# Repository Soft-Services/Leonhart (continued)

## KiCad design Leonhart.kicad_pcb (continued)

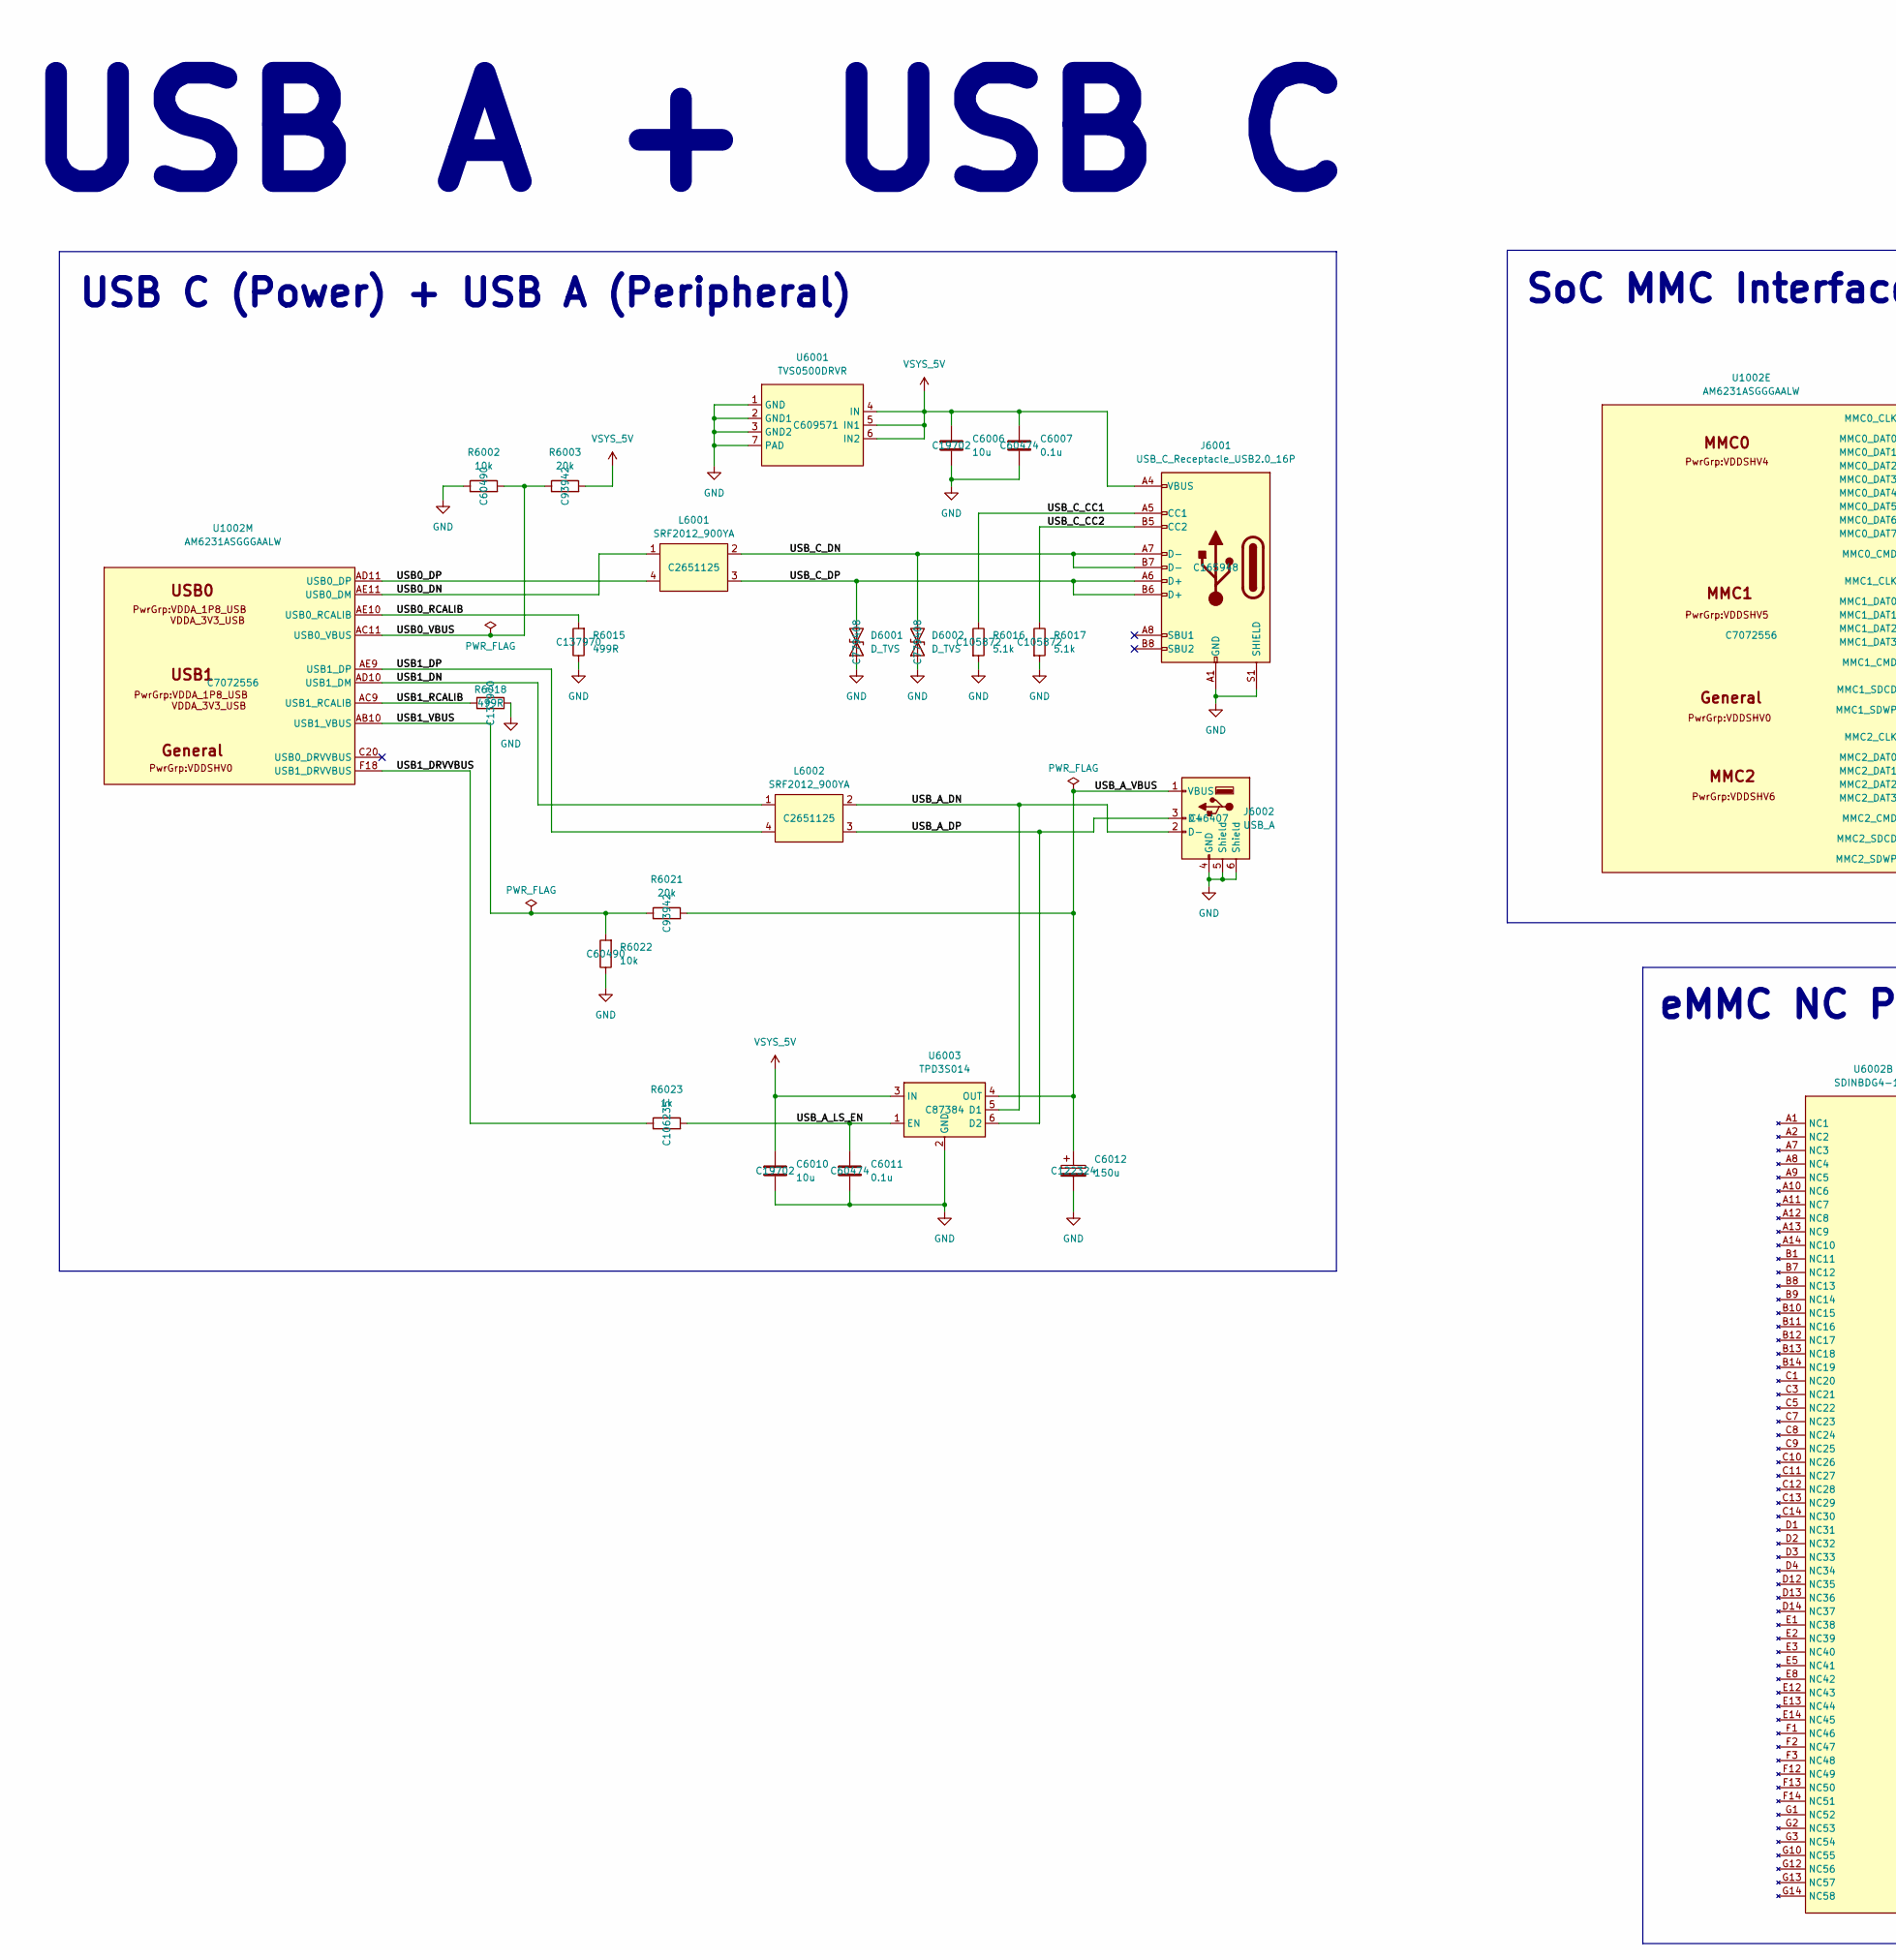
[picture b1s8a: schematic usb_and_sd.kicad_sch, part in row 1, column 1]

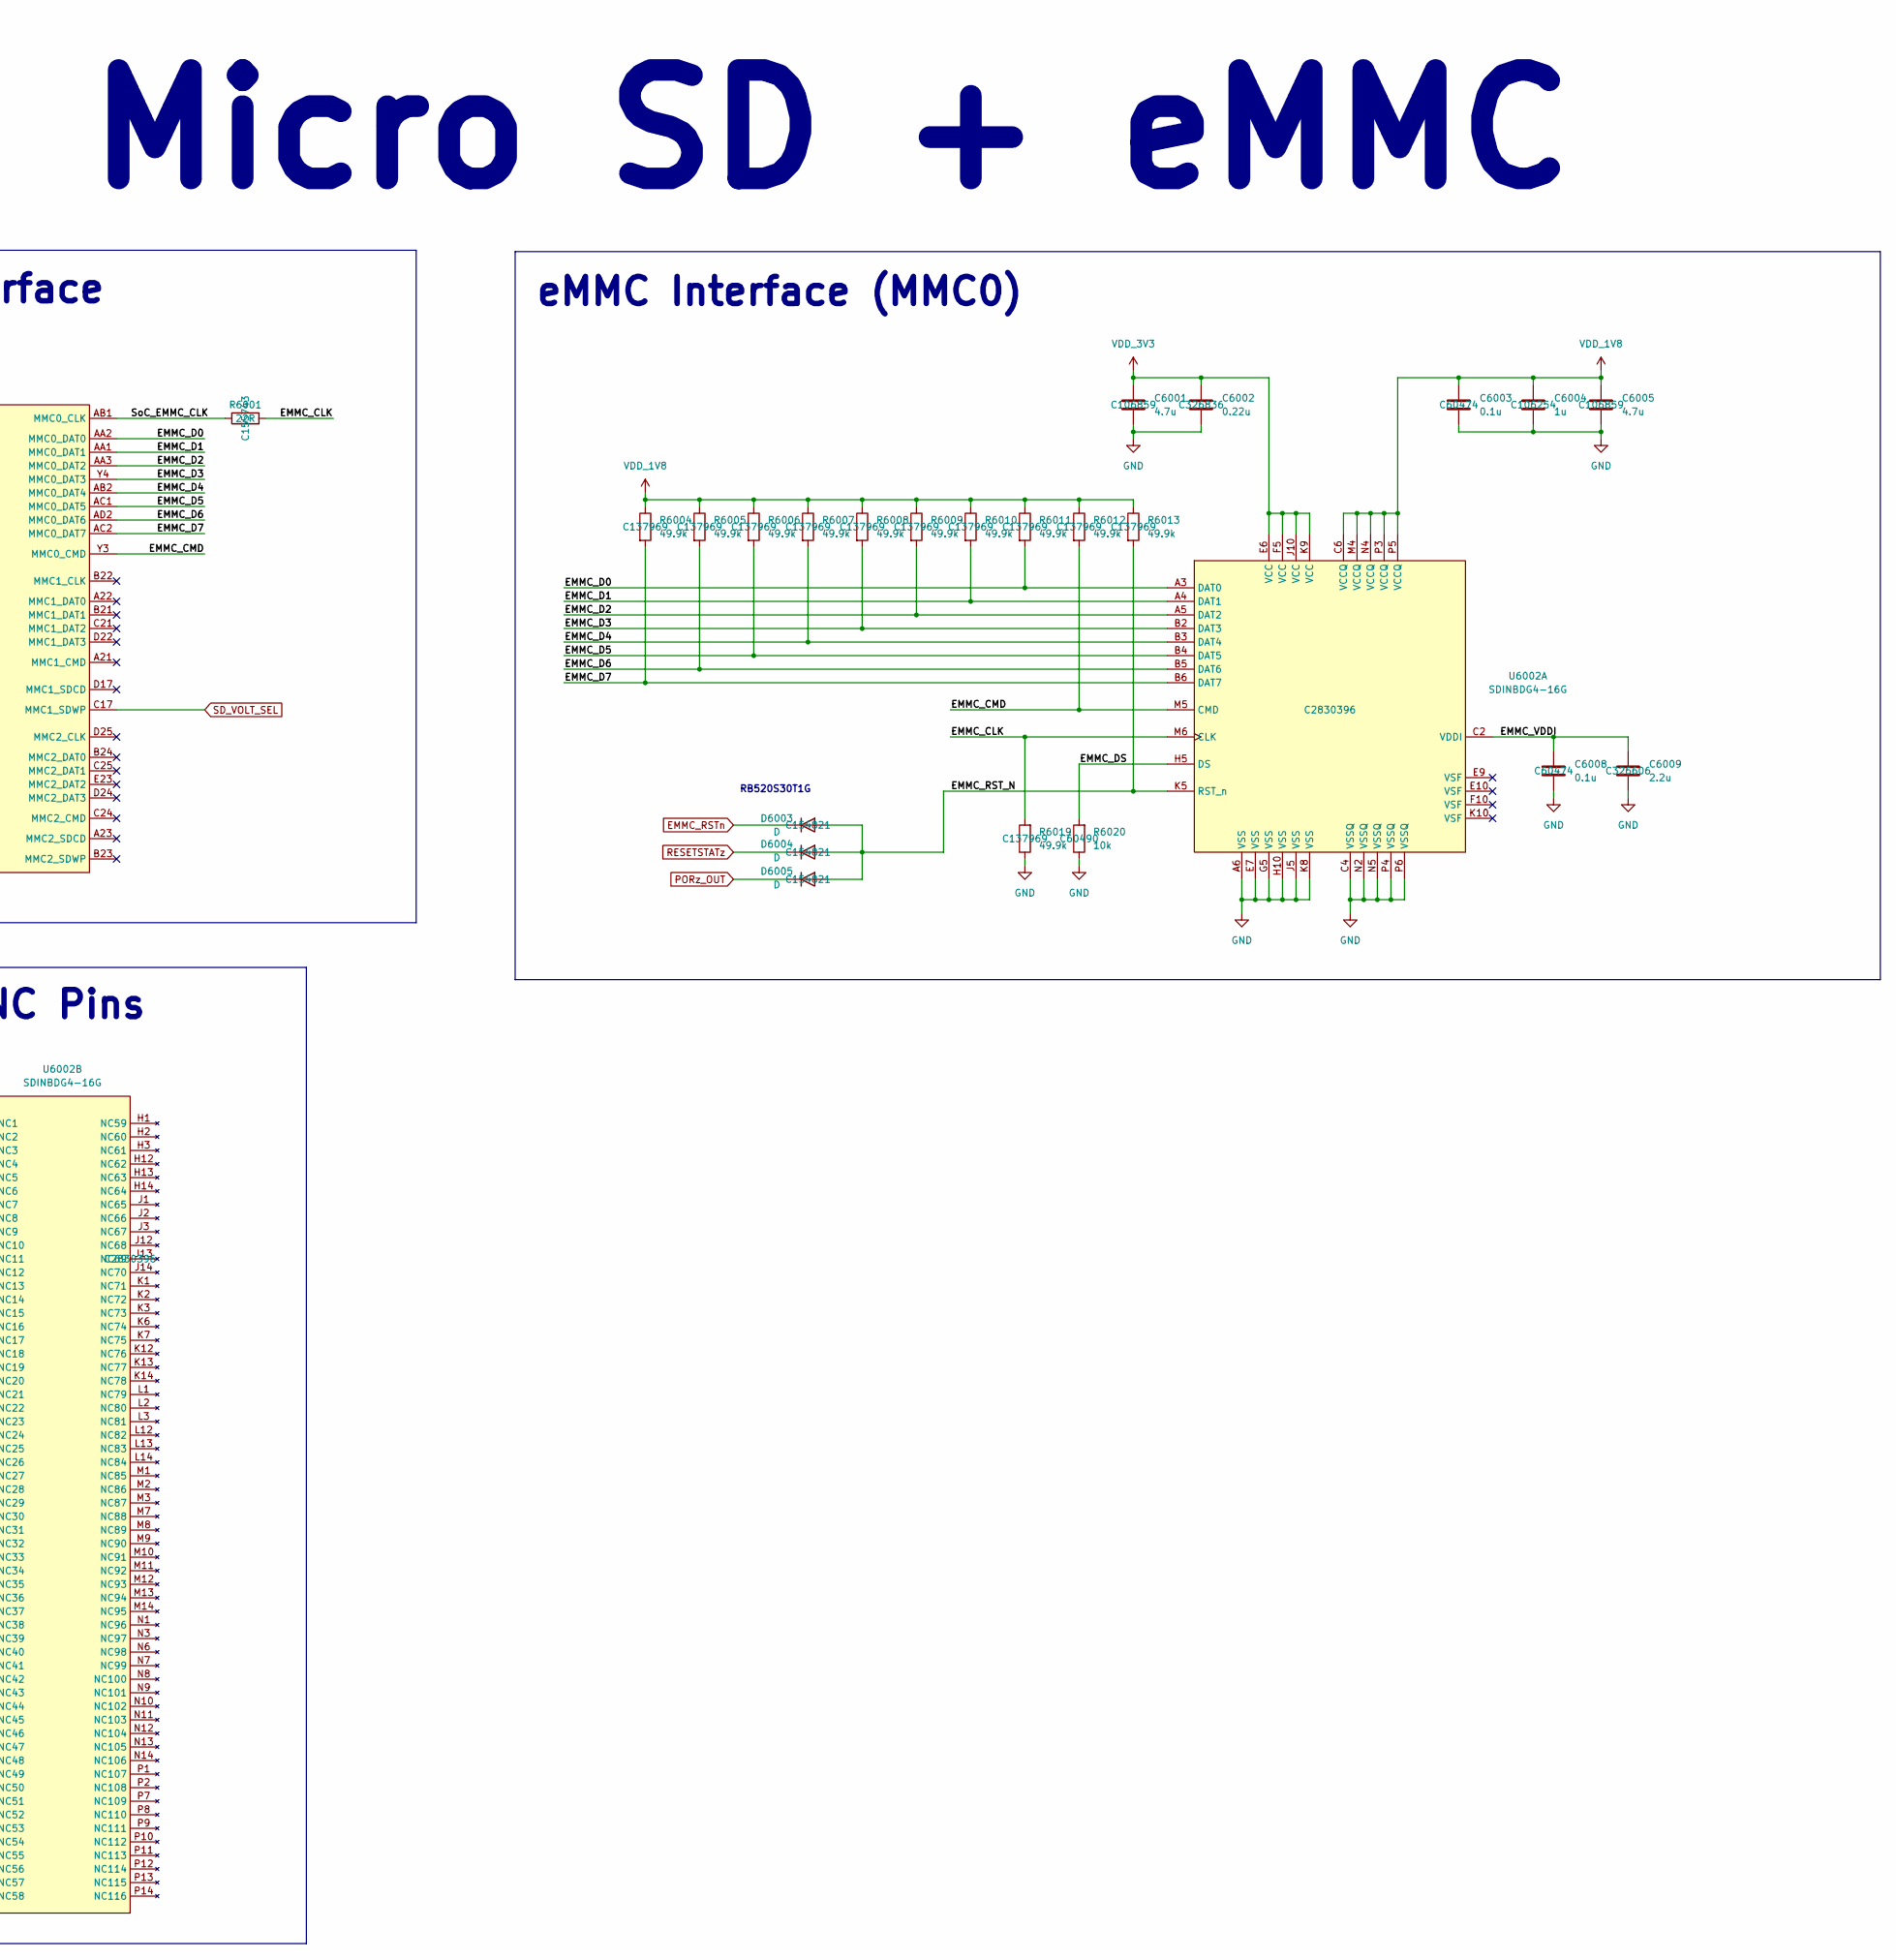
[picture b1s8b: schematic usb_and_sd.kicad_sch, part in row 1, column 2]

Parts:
C6001, C6005: 4.7u; C_0402_1005Metric; JLCPCB Part# C106859
C6002: 0.22u; C_0402_1005Metric; JLCPCB Part# C326836
C6003, C6007, C6008, C6011: 0.1u; C_0402_1005Metric; JLCPCB Part# C60474
C6004: 1u; C_0402_1005Metric; JLCPCB Part# C106254
C6006, C6010: 10u; C_0603_1608Metric; JLCPCB Part# C19702
C6009: 2.2u; C_0402_1005Metric; JLCPCB Part# C326606
C6012: 150u; CP_EIA-7343-31_Kemet-D; JLCPCB Part# C122324
D6001, D6002: D_TVS; TPD1E1B04DPYR; JLCPCB Part# C779408
D6003, D6004, D6005: D; D_SOD-523; JLCPCB Part# C154821
J6001: USB_C_Receptacle_USB2.0_16P; USB_C_Receptacle_HRO_TYPE-C-31-M-12; JLCPCB Part# C165948
J6002: USB_A; 902131A1011D10100; JLCPCB Part# C46407
L6001, L6002: SRF2012_900YA; SRF2012-900YA; JLCPCB Part# C2651125
R6001: 22R; R_0201_0603Metric; JLCPCB Part# C155743
R6002, R6020, R6022: 10k; R_0402_1005Metric; JLCPCB Part# C60490
R6003, R6021: 20k; R_0402_1005Metric; JLCPCB Part# C93942
R6004, R6005, R6006, R6007, R6008, R6009, R6010, R6011, R6012, R6013, R6019: 49.9k; R_0402_1005Metric; JLCPCB Part# C137969
R6015, R6018: 499R; R_0402_1005Metric; JLCPCB Part# C137970
R6016, R6017: 5.1k; R_0402_1005Metric; JLCPCB Part# C105872
R6023: 1k; R_0402_1005Metric; JLCPCB Part# C106235
U1002: AM6231ASGGGAALW; BGA425C50P25X25_1300X1300X89; JLCPCB Part# C7072556
U6001: TVS0500DRVR; WSON-6-1EP_2x2mm_P0.65mm_EP1x1.6mm; JLCPCB Part# C609571
U6002: SDINBDG4-16G; LFBGA-153_11.5x13mm_Layout14x14_P0.5mm; JLCPCB Part# C2830396
U6003: TPD3S014; SOT-23-6; JLCPCB Part# C87384

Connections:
/USB and MMC [6]/EMMC_CLK: R6001.2, R6019.2, U6002.M6 (CLK)
/USB and MMC [6]/EMMC_CMD: R6012.2, U1002.Y3 (MMC0_CMD), U6002.M5 (CMD)
/USB and MMC [6]/EMMC_D0: R6011.2, U1002.AA2 (MMC0_DAT0), U6002.A3 (DAT0)
/USB and MMC [6]/EMMC_D1: R6010.2, U1002.AA1 (MMC0_DAT1), U6002.A4 (DAT1)
/USB and MMC [6]/EMMC_D2: R6009.2, U1002.AA3 (MMC0_DAT2), U6002.A5 (DAT2)
/USB and MMC [6]/EMMC_D3: R6008.2, U1002.Y4 (MMC0_DAT3), U6002.B2 (DAT3)
/USB and MMC [6]/EMMC_D4: R6007.2, U1002.AB2 (MMC0_DAT4), U6002.B3 (DAT4)
/USB and MMC [6]/EMMC_D5: R6006.2, U1002.AC1 (MMC0_DAT5), U6002.B4 (DAT5)
/USB and MMC [6]/EMMC_D6: R6005.2, U1002.AD2 (MMC0_DAT6), U6002.B5 (DAT6)
/USB and MMC [6]/EMMC_D7: R6004.2, U1002.AC2 (MMC0_DAT7), U6002.B6 (DAT7)
/USB and MMC [6]/EMMC_DS: R6020.2, U6002.H5 (DS)
/USB and MMC [6]/EMMC_RST_N: D6003.2 (A), D6004.2 (A), D6005.2 (A), R6013.2, U6002.K5 (RST_n)
/USB and MMC [6]/EMMC_VDDI: C6008.1, C6009.1, U6002.C2 (VDDI)
/USB and MMC [6]/SoC_EMMC_CLK: R6001.1, U1002.AB1 (MMC0_CLK)
/USB and MMC [6]/USB0_DN: L6001.1, U1002.AE11 (USB0_DM)
/USB and MMC [6]/USB0_DP: L6001.4, U1002.AD11 (USB0_DP)
/USB and MMC [6]/USB0_RCALIB: R6015.2, U1002.AE10 (USB0_RCALIB)
/USB and MMC [6]/USB0_VBUS: R6002.2, R6003.1, U1002.AC11 (USB0_VBUS)
/USB and MMC [6]/USB1_DN: L6002.1, U1002.AD10 (USB1_DM)
/USB and MMC [6]/USB1_DP: L6002.4, U1002.AE9 (USB1_DP)
/USB and MMC [6]/USB1_DRVVBUS: R6023.1, U1002.F18 (USB1_DRVVBUS)
/USB and MMC [6]/USB1_RCALIB: R6018.2, U1002.AC9 (USB1_RCALIB)
/USB and MMC [6]/USB1_VBUS: R6021.1, R6022.2, U1002.AB10 (USB1_VBUS)
/USB and MMC [6]/USB_A_DN: J6002.2 (D-), L6002.2, U6003.5 (D1)
/USB and MMC [6]/USB_A_DP: J6002.3 (D+), L6002.3, U6003.6 (D2)
/USB and MMC [6]/USB_A_LS_EN: C6011.1, R6023.2, U6003.1 (EN)
/USB and MMC [6]/USB_A_VBUS: C6012.1, J6002.1 (VBUS), R6021.2, U6003.4 (OUT)
/USB and MMC [6]/USB_C_CC1: J6001.A5 (CC1), R6016.1
/USB and MMC [6]/USB_C_CC2: J6001.B5 (CC2), R6017.1
/USB and MMC [6]/USB_C_DN: D6002.2 (A2), J6001.A7 (D-), J6001.B7 (D-), L6001.2
/USB and MMC [6]/USB_C_DP: D6001.2 (A2), J6001.A6 (D+), J6001.B6 (D+), L6001.3
EMMC_RSTn: D6003.1 (K); also elsewhere on the board
GND: C6001.2, C6002.2, C6003.2, C6004.2, C6005.2, C6006.2, C6007.2, C6008.2, C6009.2, C6010.2, C6011.2, C6012.2, D6001.1 (A1), D6002.1 (A1), J6001.A1 (GND), J6001.A12 (GND), J6001.B1 (GND), J6001.B12 (GND), J6001.S1 (SHIELD), J6002.4 (GND), J6002.5 (Shield), J6002.6 (Shield), R6002.1, R6015.1, R6016.2, R6017.2, R6018.1, R6019.1, R6020.1, R6022.1, U6001.1 (GND), U6001.2 (GND1), U6001.3 (GND2), U6001.7 (PAD), U6002.A6 (VSS), U6002.C4 (VSSQ), U6002.E7 (VSS), U6002.G5 (VSS), U6002.H10 (VSS), U6002.J5 (VSS), U6002.K8 (VSS), U6002.N2 (VSSQ), U6002.N5 (VSSQ), U6002.P4 (VSSQ), U6002.P6 (VSSQ), U6003.2 (GND); also elsewhere on the board
PORz_OUT: D6005.1 (K); also elsewhere on the board
RESETSTATz: D6004.1 (K); also elsewhere on the board
SD_VOLT_SEL: U1002.C17 (MMC1_SDWP); also elsewhere on the board
VDD_1V8: C6003.1, C6004.1, C6005.1, R6004.1, R6005.1, R6006.1, R6007.1, R6008.1, R6009.1, R6010.1, R6011.1, R6012.1, R6013.1, U6002.C6 (VCCQ), U6002.M4 (VCCQ), U6002.N4 (VCCQ), U6002.P3 (VCCQ), U6002.P5 (VCCQ); also elsewhere on the board
VDD_3V3: C6001.1, C6002.1, U6002.E6 (VCC), U6002.F5 (VCC), U6002.J10 (VCC), U6002.K9 (VCC); also elsewhere on the board
VSYS_5V: C6006.1, C6007.1, C6010.1, J6001.A4 (VBUS), J6001.A9 (VBUS), J6001.B4 (VBUS), J6001.B9 (VBUS), R6003.2, U6001.4 (IN), U6001.5 (IN1), U6001.6 (IN2), U6003.3 (IN); also elsewhere on the board

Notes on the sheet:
USB C (Power) + USB A (Peripheral)
eMMC Interface (MMC0)
Micro SD + eMMC
RB520S30T1G
SoC MMC Interface
eMMC NC Pins
USB A + USB C

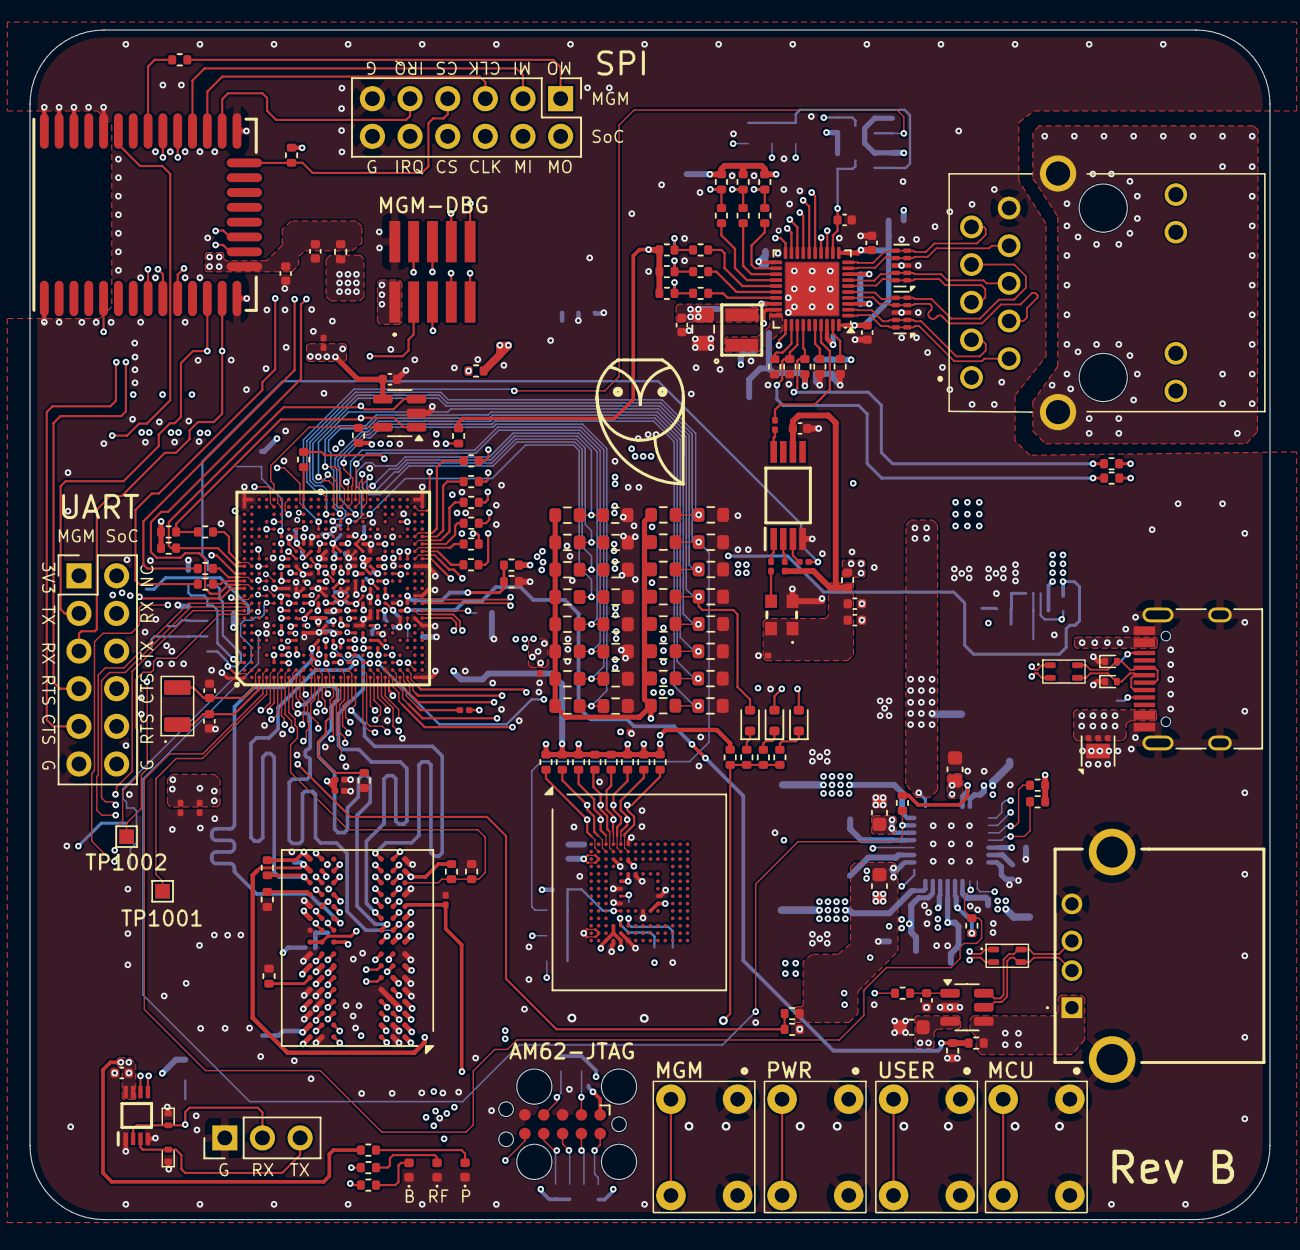
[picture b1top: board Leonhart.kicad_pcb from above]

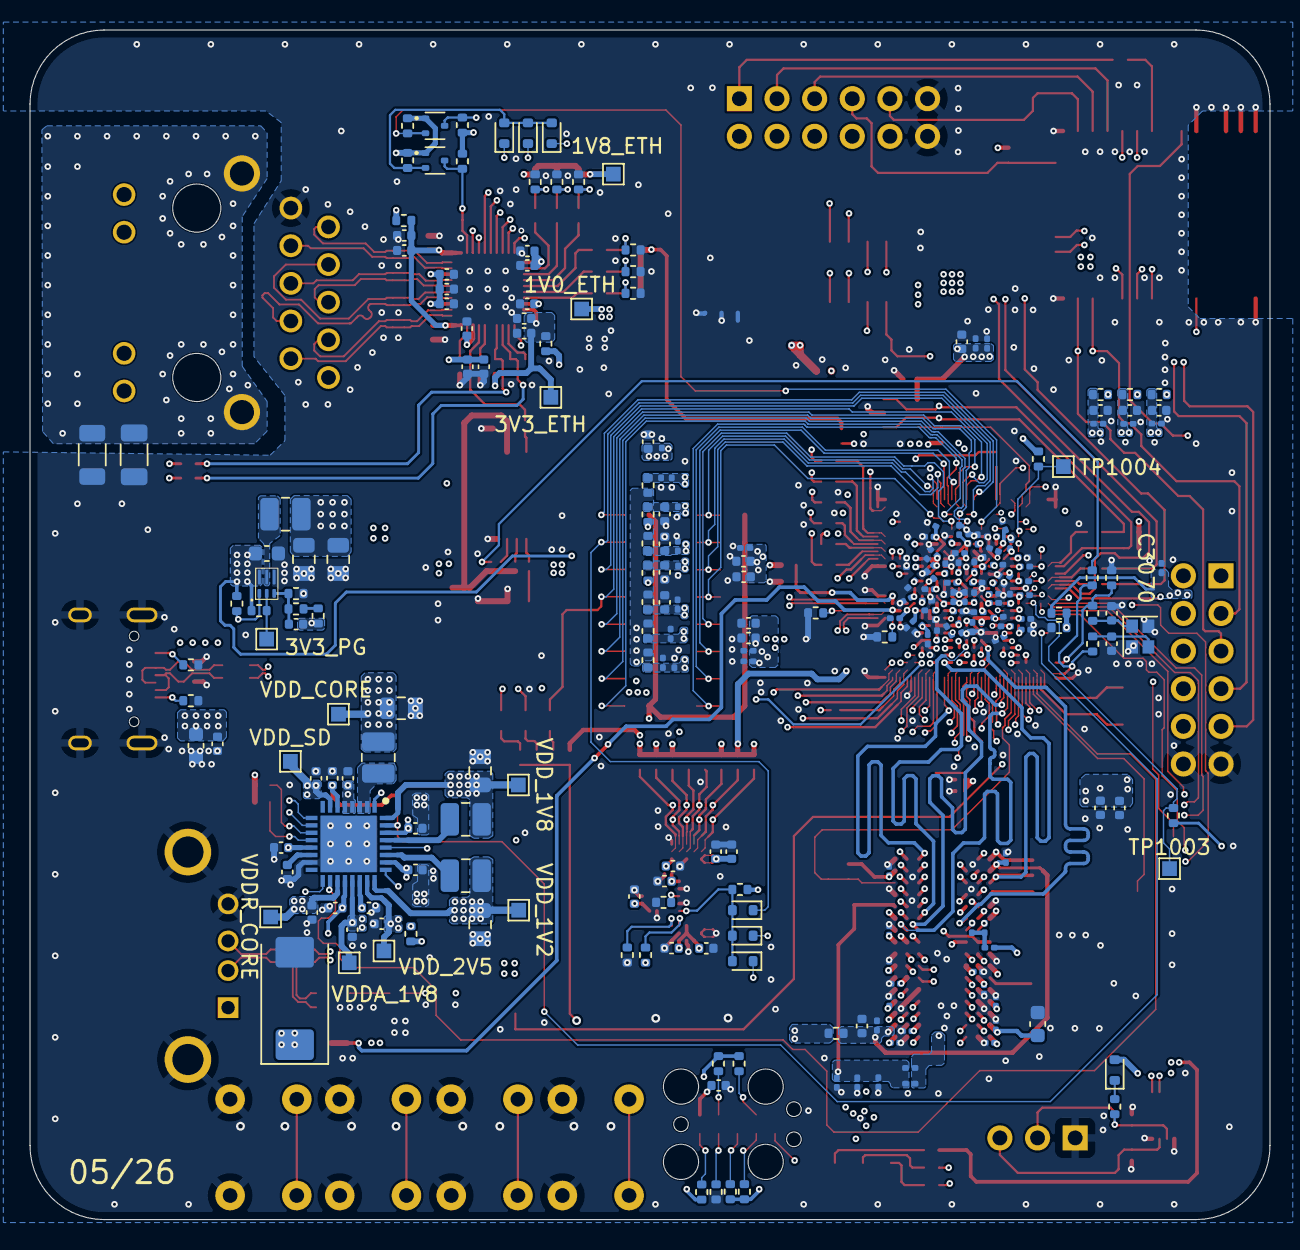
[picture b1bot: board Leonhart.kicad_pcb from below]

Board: 8 copper layers, 83.7 x 80.3 mm, 422 parts (245 on the bottom side), 275 nets.

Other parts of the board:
1V0_ETH, 1V8_ETH, 3V3_ETH, 3V3_PG: TestPoint; TestPoint_Pad_1.0x1.0mm
VDDA_1V8: TestPoint; TestPoint_Pad_1.0x1.0mm
VDDR_CORE: TestPoint; TestPoint_Pad_1.0x1.0mm
VDD_1V2, VDD_1V8, VDD_2V5: TestPoint; TestPoint_Pad_1.0x1.0mm
VDD_CORE: TestPoint; TestPoint_Pad_1.0x1.0mm
VDD_SD: TestPoint; TestPoint_Pad_1.0x1.0mm

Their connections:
/Power Circuitry [3]/VDD_3V3_PG: 3V3_PG.1; also elsewhere on the board
DVDD3V3_ETH: 3V3_ETH.1; also elsewhere on the board
VDD1V0_ETH: 1V0_ETH.1; also elsewhere on the board
VDD1V8_ETH: 1V8_ETH.1; also elsewhere on the board
VDDA_1V8: VDDA_1V8.1; also elsewhere on the board
VDDR_CORE: VDDR_CORE.1; also elsewhere on the board
VDD_1V2: VDD_1V2.1; also elsewhere on the board
VDD_1V8: VDD_1V8.1; also elsewhere on the board
VDD_2V5: VDD_2V5.1; also elsewhere on the board
VDD_CORE: VDD_CORE.1; also elsewhere on the board
VDD_SD: VDD_SD.1; also elsewhere on the board

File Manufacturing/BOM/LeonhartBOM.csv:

Comment,Designator,Footprint,JLCPCB Part#
USB_A,J6002,902-131A1011D10100:902131A1011D10100,C46407
AM6231ASGGGAALW,U1002,AM6231ASGGGAALW:BGA425C50P25X25_1300X1300X89,C7072556
0.01u,"C1001,C3092,C3095,C3098,C3101,C3104,C3107,C3110,C3113,C3116,C3119,C4004,C4006,C4007,C4008,C4009,C4010,C4011,C4012,C4013,C4014,C4015,C4016,C4017",Capacitor_SMD:C_0201_0603Metric, C272853
1u,"C3023,C3024,C3025,C3026,C3027,C3028,C3029,C3030,C3031,C3034,C3062,C3074,C3084,C3093,C3102,C3117",Capacitor_SMD:C_0201_0603Metric, C272877
0.1u,"C3035,C3036,C3037,C3038,C3039,C3040,C3041,C3042,C3043,C3044,C3045,C3046,C3047,C3048,C3049,C3053,C3054,C3055,C3056,C3057,C3058,C3059,C3060,C3063,C3064,C3065,C3066,C3067,C3068,C3069,C3070,C3071,C3072,C3075,C3076,C3077,C3078,C3079,C3080,C3081,C3085,C3086,C3087,C3088,C3089,C3091,C3094,C3097,C3100,C3103,C3106,C3109,C3112,C3115,C3118,C3120,C3121,C3122,C3123,C4002,C4003,C4018,C4019,C4020,C4021",Capacitor_SMD:C_0201_0603Metric,C190183
1u,"C1002,C2001,C3108,C3111,C6004,C6014",Capacitor_SMD:C_0402_1005Metric, C106254
0.1u,"C1003,C1004,C1009,C1010,C1011,C2002,C3002,C3005,C3008,C5001,C5002,C5004,C5005,C5007,C5008,C5009,C5010,C5012,C5013,C5015,C5017,C5019,C5020,C6003,C6007,C6008,C6011,C6015",Capacitor_SMD:C_0402_1005Metric,C60474
18p,"C1005,C1006",Capacitor_SMD:C_0402_1005Metric,C88878
20p,"C1007,C1008",Capacitor_SMD:C_0402_1005Metric,C107000
2.2u,"C3010,C3011,C3013,C3014,C3015,C3016,C3017,C3018,C4001,C6009",Capacitor_SMD:C_0402_1005Metric, C326606
4.7u,"C3012,C3033,C3052,C3061,C3073,C3083,C3090,C3096,C3099,C3105,C3114,C5003,C5006,C5011,C5014,C5016,C5018,C6001,C6005",Capacitor_SMD:C_0402_1005Metric, C106859
120p,C3020,Capacitor_SMD:C_0402_1005Metric, C161146
10u,"C3032,C3051,C3082",Capacitor_SMD:C_0402_1005Metric,C962143
0.22u,C6002,Capacitor_SMD:C_0402_1005Metric,C326836
10u,"C3001,C3004,C3007,C3019,C6006,C6010",Capacitor_SMD:C_0603_1608Metric, C19702
22u,C4005,Capacitor_SMD:C_0603_1608Metric,C84419
4.7u,C6013,Capacitor_SMD:C_0603_1608Metric, C1705
47u,"C3003,C3006,C3009",Capacitor_SMD:C_0805_2012Metric, C109461
22u,"C3021,C3022,C6016,C6017",Capacitor_SMD:C_0805_2012Metric,C784585
1n,C5021,Capacitor_SMD:C_1206_3216Metric, C23631
150u,C6012,Capacitor_Tantalum_SMD:CP_EIA-7343-31_Kemet-D,C122324
TC2050,"J1002,J2001",Connector:Tag-Connect_TC2050-IDC-NL_2x05_P1.27mm_Vertical,
Conn_01x03_Pin,J1003,Connector_PinHeader_2.54mm:PinHeader_1x03_P2.54mm_Vertical,C49257
Conn_01x06_Pin,"J1001,J1004,J2002,J2003",Connector_PinHeader_2.54mm:PinHeader_1x06_P2.54mm_Vertical,C37208
USB_C_Receptacle_USB2.0_16P,J6001,Connector_USB:USB_C_Receptacle_HRO_TYPE-C-31-M-12,C165948
25MHz,X1002,Crystal:Crystal_SMD_2016-4Pin_2.0x1.6mm,C127893
D,"D1001,D1002,D1003,D1004,D5001,D5002,D5003,D6003,D6004,D6005,D6013,D6014",Diode_SMD:D_SOD-523,C154821
ECS-2520MV-250-CN-TR,X1001,ECS-2520MV-250-CN-TR:ECS2520MV250CNTR,C405464
HR911130A,U5001,HR911130A:HR911130A,C54408
0.47u,"L3001,L3002,L3003,L3004",Inductor_SMD:L_1008_2520Metric,C237552
Red,D7001,LED_SMD:LED_0402_1005Metric,C165980
Green,D7002,LED_SMD:LED_0402_1005Metric,C165979
Blue,D7003,LED_SMD:LED_0402_1005Metric,C165977
LMK1C1102PWR,U1001,LMK1C1102PWR:SOP65P640X120-8N,C2859546
MGM240PB32VNA3,U2001,MGM240PB32VNA3:MGM240PB32VNA3,C20441846
K4AAG165WA-BCWE,U4001,Package_BGA:FBGA-96_9x13mm_Layout9x16_P0.8mm,C2920140
SDINBDG4-16G,U6002,Package_BGA:LFBGA-153_11.5x13mm_Layout14x14_P0.5mm,C2830396
RTL8211F-CG,U5002,Package_DFN_QFN:QFN-40-1EP_5x5mm_P0.4mm_EP3.6x3.6mm,C187932
TPD4E05U06DQA,"U5003,U5004",Package_SON:USON-10_2.5x1.0mm_P0.5mm,C138714
TVS0500DRVR,U6001,Package_SON:WSON-6-1EP_2x2mm_P0.65mm_EP1x1.6mm,C609571
DMG1012T,"Q5001,Q5002",Package_TO_SOT_SMD:SOT-523,C20512
AT24C32D-STUM-T,U1004,Package_TO_SOT_SMD:SOT-23-5,C2061176
TPD3S014,U6003,Package_TO_SOT_SMD:SOT-23-6,C87384
10k,R1020,Resistor_SMD:R_0201_0603Metric,C106225
22R,"R1021,R1022,R1023,R6001",Resistor_SMD:R_0201_0603Metric,C155743
33R,"R4001,R4002",Resistor_SMD:R_0201_0603Metric, C295794
1k,"R4009,R4010",Resistor_SMD:R_0201_0603Metric,C138165
120R,"FB1001,FB2001,FB3001,FB3002,FB3003,FB3004,FB3005,FB3006,FB3007,FB3008,FB3009,FB3010,FB3011,FB4001,FB5001,FB5002",Resistor_SMD:R_0402_1005Metric,C76891
10k,"R1001,R1018,R1019,R1054,R1055,R1056,R1057,R1058,R1059,R1060,R1061,R2002,R3003,R3004,R3005,R3006,R3007,R3009,R3010,R3011,R4005,R5028,R5029,R5030,R5031,R6002,R6020,R6022,R6024,R6025,R6026,R6028,R6029,R6030,R6031",Resistor_SMD:R_0402_1005Metric,C60490
1k,"R1024,R1025,R1026,R4008,R6023",Resistor_SMD:R_0402_1005Metric,C106235
2.2k,"R1043,R1044,R4004,R7001,R7002,R7003",Resistor_SMD:R_0402_1005Metric,C114762
0R,"R1045,R1053",Resistor_SMD:R_0402_1005Metric,C106231
22R,"R1046,R1049,R1051,R2001,R5008,R5009,R5010,R5011,R5012,R5013,R5014,R5015,R5016,R5017,R5018,R5019,R5021,R6014",Resistor_SMD:R_0402_1005Metric,C114765
R,"R1047,R1052,R3008,R4003,R5001,R5002,R5032,R5033,R5034,R5037",Resistor_SMD:R_0402_1005Metric,
470R,R1048,Resistor_SMD:R_0402_1005Metric,C114877
100k,"R3001,R3014",Resistor_SMD:R_0402_1005Metric,C60491
11k,R3002,Resistor_SMD:R_0402_1005Metric,C138063
270k,R3012,Resistor_SMD:R_0402_1005Metric,C163475
180k,R3013,Resistor_SMD:R_0402_1005Metric, C138046
240R,"R4006,R4007",Resistor_SMD:R_0402_1005Metric,C114755
4.7k,"R5003,R5005,R5006,R5007,R5020,R5022,R5024,R5035,R5036",Resistor_SMD:R_0402_1005Metric,C105871
1.5k,R5004,Resistor_SMD:R_0402_1005Metric,C114759
2.49k,R5023,Resistor_SMD:R_0402_1005Metric,C145071
510R,"R5025,R5026",Resistor_SMD:R_0402_1005Metric, C276273
1M,R5027,Resistor_SMD:R_0402_1005Metric,C108083
20k,"R6003,R6021",Resistor_SMD:R_0402_1005Metric,C93942
49.9k,"R6004,R6005,R6006,R6007,R6008,R6009,R6010,R6011,R6012,R6013,R6019",Resistor_SMD:R_0402_1005Metric,C137969
499R,"R6015,R6018",Resistor_SMD:R_0402_1005Metric,C137970
5.1k,"R6016,R6017",Resistor_SMD:R_0402_1005Metric,C105872
10k,R6027,Resistor_SMD:R_0402_1005Metric,C60490
R,"R1002,R1003,R1005,R1009,R1010,R1012,R1013,R1015,R1029,R1031,R1032,R1033,R1036,R1039,R1041,R1042",Resistor_SMD:R_0603_1608Metric,
10k,"R1004,R1006,R1007,R1008,R1011,R1014,R1016,R1017,R1027,R1028,R1030,R1034,R1035,R1037,R1038,R1040",Resistor_SMD:R_0603_1608Metric, C98220
SN74LVC2G241DCUR,U1003,SN74LVC2G241DCUR:SOP50P310X90-8N,C10430
1u,C3124,SoftServicesFootprintLibrary:0201_Cap_Leonhart, C272877
SW_MEC_5E,"SW7001,SW7002,SW7003,SW7004",SoftServicesFootprintLibrary:1825910-6,C428628
2.2u,L5001,SoftServicesFootprintLibrary:CVH201610A-2R2M,C391305
32.768kHz,X1003,SoftServicesFootprintLibrary:FC-135R 32.7680KA-A3, C6554955
SRF2012_900YA,"L6001,L6002",SoftServicesFootprintLibrary:SRF2012-900YA,C2651125
TLV62595DMQR,U3002,SoftServicesFootprintLibrary:TLV62595DMQR,C3189969
D_TVS,"D1005,D1006,D6001,D6002,D6006,D6007,D6008,D6009,D6010,D6011,D6012",SoftServicesFootprintLibrary:TPD1E1B04DPYR,C779408
TestPoint,"TP1001,TP1002,TP1003,TP1004,TP3001,TP3002,TP3003,TP3004,TP3005,TP3006,TP3007,TP3008",TestPoint:TestPoint_Pad_1.0x1.0mm,
Micro_SD_Card_Det1,J6003,TF-15x15:TF15X15,C7301403
TPS22918DBVR,U6004,TPS22918DBVR:SOT95P280X145-6N,C131941
TPS6521903RHBR,U3001,TPS6521903RHBR:QFN50P500X500X100-33N-D,C18716455

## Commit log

2025-08-04 Added KiCad files
2025-08-05 Added few custom block symbols for AM6231
2025-08-05 Finished splitting up AM6231 schematic symbol into groups
2025-08-05 Added more custom schematic symbols
2025-08-06 Started power circuitry and added more custom schematic symbols
2025-08-06 Finished CC2652P schematic
2025-08-06 Fixed schematic symbol errors
2025-08-07 Added some net labels and schematic routing
2025-08-07 Worked on schematic for DDR4 memory
2025-08-08 Finished DDR4 schematic + relevant circuity and started SoC power
2025-08-08 Added USB A and USB C to the schematic
2025-08-09 Added micro SD card circuitry
2025-08-10 Added power pins and confirmed power source + some current requirements
2025-08-10 Fixed some power distribution and grouping
2025-08-10 Simplified SoC blocks
2025-08-11 Finished CC2652P and UART2
2025-08-11 Small fixes
2025-08-13 Fixed power issues
2025-08-14 Added some Ethernet circuitry and fixed schematic symbols
2025-08-18 Added eMMc
2025-08-18 Added SoC and eMMC reset logic. Also SD power logic
2025-08-18 Added thread symbol and circuitry
2025-08-19 Added power management for nRF52840
2025-08-19 Added more thread circuitry
2025-08-19 Almost finished Ethernet schematic
2025-08-19 Added thread circuitry
2025-08-20 Fixed errors and added TI sysconfig file for AM6231
2025-08-20 Assigned more pins in sysconfig
2025-08-20 Added more to sysconfig and wkup domain on schematic
2025-08-21 Fixed balun matching network for CC2652P
2025-08-21 Fixed net labels and added Ethernet reset digital logic. Also continued to update pinmux on TI sysconfig
2025-08-21 Tidied up schematic
2025-08-22 Fixed small issues
2025-08-23 Added CC2652PSIP schematic symbol. Switching out for CC2652P for RF simplicity
2025-08-25 Fixed SoC power circuitry
2025-08-25 Fixed pinmux issues that came with power issues
2025-08-25 Finished SoC schematic
2025-08-25 Finished overall schematic. Fixing errors and warnings from ERC
2025-08-25 Fixed more errors and warnings
2025-08-26 Fixed ERC errors and warnings (zero errors and zero warnings)
2025-08-26 Labeled all nets and added some footprints
2025-08-27 Added some footprints for important ICs
2025-08-27 Added more IC footprints
2025-08-27 Added more footprints
2025-08-28 Added many more footprints
2025-08-28 More footprints
2025-08-28 Finished IC and crystal footprints
2025-08-29 Double checked power, ddr4, USB, MMC and added bootstrap. Also added buttons and added pinmuxing in sysconfig
2025-08-29 Small changes
2025-08-29 Added header pins for UART5
2025-08-29 Added board stackup JLC08081H-1080
2025-08-30 Added capcitor footprints
2025-08-31 Added almost all passive component footprints
2025-08-31 Added net classes and colouring on layout editor
2025-09-01 Fixed footprint issues to comply with manufacturer constraints
2025-09-01 More layout
2025-09-02 Did fanout for SoC BGA power balls
2025-09-03 Added necessary nRF52840 SPI logic circuitry and GPIOs. Also added pinmux
2025-09-03 More SoC fanout
2025-09-04 Fixed SoC power fanout with updated constraints and stackup
2025-09-05 Did byte swapping on DDR for easier routing
2025-09-06 Completed DDR4 dogbone fanout
2025-09-08 Fixed stackup started DDR4 routing
2025-09-08 Fixed DDR data routing
2025-09-08 Did more DDR4 routing
2025-09-10 Did more SoC power decoupling routing
2025-09-10 More SoC power cap placement
2025-09-11 Cleaned up schematic
2025-09-13 Restarted SoC power decoupling based on manufacturer capabilities
2025-09-15 Added more SoC powering decaps
2025-09-16 More SoC power decap placement
2025-09-16 Fixed SoC power decap placements
2025-09-16 More capacitor placement
2025-09-16 More SoC decaps
2025-09-17 Solved PDN capacitor placement space issue
2025-09-17 Almost finished SoC PDN
2025-09-18 Finished SoC PDN
2025-09-18 Placed all DDR4 escape vias
2025-09-18 Finished DDR4 address geometry
2025-09-19 Finished connecting DDR4 pins and adding return vias
2025-09-20 Changed DDR4 decoupling capacitors and placed them
2025-09-21 Shuffled SoC decaps around for priority caps. Fixed DRC violations
2025-09-21 Added DDR4 device power decoupling and prepped byte lane traces for length matching
2025-09-21 Small clearance changes
2025-09-22 Started DDR4 length matching
2025-09-22 Matched DDR4 byte 0
2025-09-22 More DDR length matching
2025-09-24 Length matched other DDR byte but might readjust for SI improvement
2025-09-25 More DDR4 tuning
2025-09-25 Placed all DDR4 external circuitry and added power puddles
2025-09-26 Started DDR address length matching
2025-09-29 Finished DDR4 length matching
2025-09-29 Added clock buffor for CMOS 25MHz osc. Used for both SoC and Ethernet with optional SoC crystal still placed
2025-09-30 Started USB and OSC routing
2025-10-01 Continued Ethernet routing
2025-10-01 More Ethernet routing. Also replaced SMA connectors with RF switch and plan to use microstrip antenna
2025-10-02 Routed 5V -> 3.3V Buck converter and started PMIC routing and power planes
2025-10-02 Added RJ45 connector chassis ground plane and vias
2025-10-02 Routed out PMIC
2025-10-03 Routed most of Ethernet PHY and RGMII
2025-10-04 Polished and partly routed eMMC
2025-10-04 Continued routing Ethernet PHY external circuitry. Added ESD protection diode arrays to Ethernet
2025-10-05 Length tuned Ethernet lines
2025-10-06 Routed eMMC and finished length tuning RGMII
2025-10-06 Continued PDN routing
2025-10-06 Improved clock layout and clock PDN
2025-10-08 Finished USB A routing. Started micro sd routing
2025-10-08 More micro SD routing
2025-10-09 Switched out CC2652P and nRF52840 for MGM240P to run Zigbee and Thread
2025-10-09 Added new radio schematic
2025-10-09 Testing branch
2025-10-09 Restarted DDR4 routing with new stackup
2025-10-13 Routed DDR4 addresses and command signals. Started length matching
2025-10-14 Finished length matching byte lanes to respective strobe
2025-10-14 Finished DDR4 address length matching
2025-10-14 Finished DDR4 routing with new stackup
2025-10-16 Added UART and SPI header pins for MGM240P module options
2025-10-16 Moved around subsections and rerouted RGMII, USBA and USBC
2025-10-18 Laid out and routed boot mode resistors
2025-10-19 Length matched eMMC
2025-10-20 Finished micro SD length matching
2025-10-20 Routed SD load switch and system control traces
2025-10-25 Routed JTAG and UART header pins for SoC
2025-10-26 Routed all SPI traces. Also started fixing default trace widths to round metric numbers
2025-10-27 Added and routed Micro SD load switch
2025-10-27 Placed more pull up resistors and diodes
2025-10-28 Routed I2C traces and some reset traces
2025-10-28 Started PDN power islands routing
2025-10-29 Created VDDR_CORE and VDD_1V2 power islands
2025-10-30 Placed ferrite beads and relevant decoupling caps for analog 1.8V rails
2025-10-31 Routed more analog and core power rails
2025-11-02 More PDN power planes
2025-11-03 Routed more power planes for VDD_3V3 and VDD_1V8
2025-11-07 Fixed some DRC errors
2025-11-08 Routed all power rails to AM6231 SoC
2025-11-09 More PDN routing
2025-11-10 Routed more power (for VDD_1V8)
2025-11-12 Routed buttons and added some return vias. Fixed power distribution problem
2025-11-12 Added more return and stitching vias
2025-11-13 Placed bulk decaps for VDDR_CORE and VDD_CORE
2025-11-13 Placed bulk decaps for VDD_3V3 and VDD_1V8 finishing the placement of bulk decaps
2025-11-14 Added stitching vias arround DDR4
2025-11-14 Added ground copper fill to L1 and L8
2025-12-22 Started redoing L5 of DDR4 routing
2025-12-22 Removed DDR4 L5 traces
2025-12-22 Routed byte 0 of DDR4
2025-12-24 More DDR4 routing
2025-12-25 Finished rerouting of DDR4 L5
2025-12-25 Small cleanup
2025-12-26 Small schematic naming change and added silkscreen to buttons and header pins
2025-12-26 GND stitching vias placed around board edge. DDR4 L2 needs to be redone
2025-12-26 Started rerouting of DDR4 L2
2026-01-01 Finishing up DDR4 L2 length tuning
2026-01-02 Finished DDR4 routing 3rd iteration
2026-01-02 Small clean up
2026-01-03 Fixed more errors and connected VDDR_CORE bulk caps to main rail
2026-01-03 Fixed DRC errors and added extra ground vias in PMIC area
2026-01-05 Fixed a few errors and created test gerber files
2026-01-07 Added ground vias to USB and PMIC+Buck sections
2026-01-07 More error fixing
2026-01-10 Fixed all warnings and almost all errors in DRC
2026-01-12 Added status LEDs for SoC power, MGM240P power, and for GPIO0_70
2026-01-13 Fixed silkscreen of footprint for DDR4 module
2026-01-14 Chose better inductor for ethernet phy 1.0V rail
2026-02-06 Added JLCPCB part numbers for some caps
2026-02-06 All capacitors and crystals added to BOM. 150u cap for USB A changed to tantalum and rerouted
2026-02-06 Added diode and tvs diode JLC part numbers to BOM. Also fixed tvs diode footprint
2026-02-06 All JLC part numbers added to BOM except LEDs
2026-02-07 Finished adding JLC part numbers to BOM
2026-02-08 Changed ethernet phy strap options and added DNP options for debugging
2026-02-09 Small fixes and cleanup
2026-02-10 Fixed tolerence issues. Fixed LF crystal layout
2026-02-15 Small DDR4 cleanup
2026-02-15 Fixed fatal DDR4 address length issue
2026-02-15 Fixed DDR4 fully
2026-02-15 EMMC length matching fixed
2026-02-15 Confirmed and fixed RGMII lengths
2026-02-15 Checked and improved SD (mmc1) length matching
2026-02-16 Added testpoints for MCU_RESETz and RESET_REQZ
2026-02-16 Small fixes and added some return ground vias
2026-02-19 Added extra decoupling capacitors and pull up resistor to MGM240P module
2026-02-23 Updated JLC part numbers
2026-02-23 Fixed RESETSTATz shorted to ground
2026-02-23 Created trial component placement, assembly, and BOM files
2026-02-25 Ordered Rev A
2026-02-27 Canceled order, fixed microSD socket footprint issue. Fixed eMMC trace width issue
2026-03-01 Fixed SD routing and made little improvements to clock area
2026-03-30 Added image to README
2026-03-30 Added more photos to README
2026-03-30 Fixed hardware photo layout
2026-03-31 Update README with USB-A controller and boot strategy
    Added USB-A controller and Linux boot strategy details.
2026-04-02 Add progress update on Linux boot status
    Added progress update on Linux booting with Arago distribution and rootfs and U-Boot files.
2026-04-02 Update README with Linux boot and power issues
    Added note about Linux boot issues and power sequencing.
2026-04-02 Small README cleanup
2026-04-05 Added progress photo to README
2026-04-08 Updated Progress #2 section in README.md
2026-05-01 Placed and routed new UART and SPI headers, routed out correct MGM240P pinout, routed out Mini Simplicity 10 pin connector, swapped legless TC2050 footprint for legged version. Need to reroute SoC JT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
2026-05-01 More SoC JTAG routing, improved PMIC signal integrity
2026-05-01 Finished routing JTAG
2026-05-02 Remove BOM file patterns from .gitignore
    Remove exported BOM files from .gitignore.
2026-05-02 Finished routing Rev B and fixed all errors and warnings
2026-05-02 Updated gitignore
2026-05-02 Cleaned up BOM folder
2026-05-03 Fixed Ethernet schematic and strapping. Also fixed some decoupling routing
2026-05-03 Finished Ethernet routing
2026-05-04 Fixed Ethernet inductor and capacitor regulator parts. Cleaned up Ethernet routing
2026-05-05 Finished Rev B. More double checking needed. Ordered Silicon Labs J Link debugger for MGM240P
2026-05-05 Small silkscreen changes
2026-05-05 Added DS_Store to .gitignore
2026-05-05 Deleted DS_Store files
2026-05-05 Ordered Rev B
2026-05-19 Added Rev B working progress update to readme
2026-05-19 testing image
2026-05-19 Small readme fix
2026-05-30 Updated readme for Rev B progress
2026-05-31 Added Progress update #6 to README.md
2026-06-02 Updated README.md file with new working Thread network chain progress
2026-06-12 Added progress update #7
2026-06-12 README cleanup
2026-06-12 Added network status screenshots to readme
2026-06-12 Updated next steps and project overview in readme
2026-06-19 README cleaning
